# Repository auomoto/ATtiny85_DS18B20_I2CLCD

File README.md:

ATtiny85_TWI_MCP23008_DS18B20_LCD
=================================

This reads a DS18B20 1-Wire temperature sensor and prints the temperature on an LCD screen controlled by an I2C MCP23008 port expander.

Work in progress; this might not work. (see the TWI_SCAN project for later versions?)

ATtiny85 details:

FUSES:	Low:0x62, High:0xDF, Extended:0xFF
	Low=0x62 is 8MHz clock with /8 divider (1MHz CPU clock)
	High=0xDF enables programming, not much else
	Extended=0xFF (no self programming)

To read fuses (lfuse, hfuse, or efuse):
	avrdude -c usbtiny -p attiny85 -U lfuse:r:-:h
	To write fuses (example):
	avrdude -c usbtiny -p attiny85 -U lfuse:w:0x62:m

=========================================================
	
STEP 1: Set up timer interrupts and light the LED.
	The init_ATtiny85() routine sets up the LED on pin 2,
	sets the timer0 clock to run at 1/1024 of the CPU clock
	(so it's 1KHz), and sets up timer interrupts using
	clear-timer-on-compare (CTC) using timer0. The value
	to compare is loaded into the output compare register
	OCR0A (8-bits).

	TTCR0A = Timer/Counter Control Register A for timer0 (set clear timer on compare, CTC, mode)
	TTCR0B = Timer/Counter Control Register B for timer0 (set prescaler by setting CS02, CS01, CS00)
		----------------------
		| CS02 | CS01 | CS00 |
		----------------------
		|   1  |   0  |   1  | is /1024
		----------------------

=========================================================

STEP 2: Set up I2C communications. For I2C, there is one #define
	(__ATtiny85__) and one #include file (usi_twi_master.c). Initialize
	the I2C interface with a call to usi_twi_master_initialize().

	The MCP23008 base address is 0x20. Insert the device address (3 bits),
	shift this left one bit and insert the r/w bit to form the address.
	The base address is handled within MCP23008Write(addr, REGISTER, data)
	so you only put in the 3-bit address as addr.
		Testing the I2C communications is done with the test lights board, an
	LED light bar with eight (out of ten) LEDs connected to the MCP23008.

STEP 2: Rev C.

=========================================================

STEP 3: Connect the LCD display. The LCD is driven off an MCP23008 at
	address 0x01.

=========================================================

STEP 4: Set up the OneWire communications.

=========================================================

STEP 5: Set up the DS18B20 routines.

=========================================================

Note: The usi_twi_master routines are old. Newer versions are in the ATtiny4313 PCA9543 project directory and should replace these. Also change the MCP23008 LCD routines to match the Adafruit backpack pinning since we'll probably buy more of those instead of making our own.

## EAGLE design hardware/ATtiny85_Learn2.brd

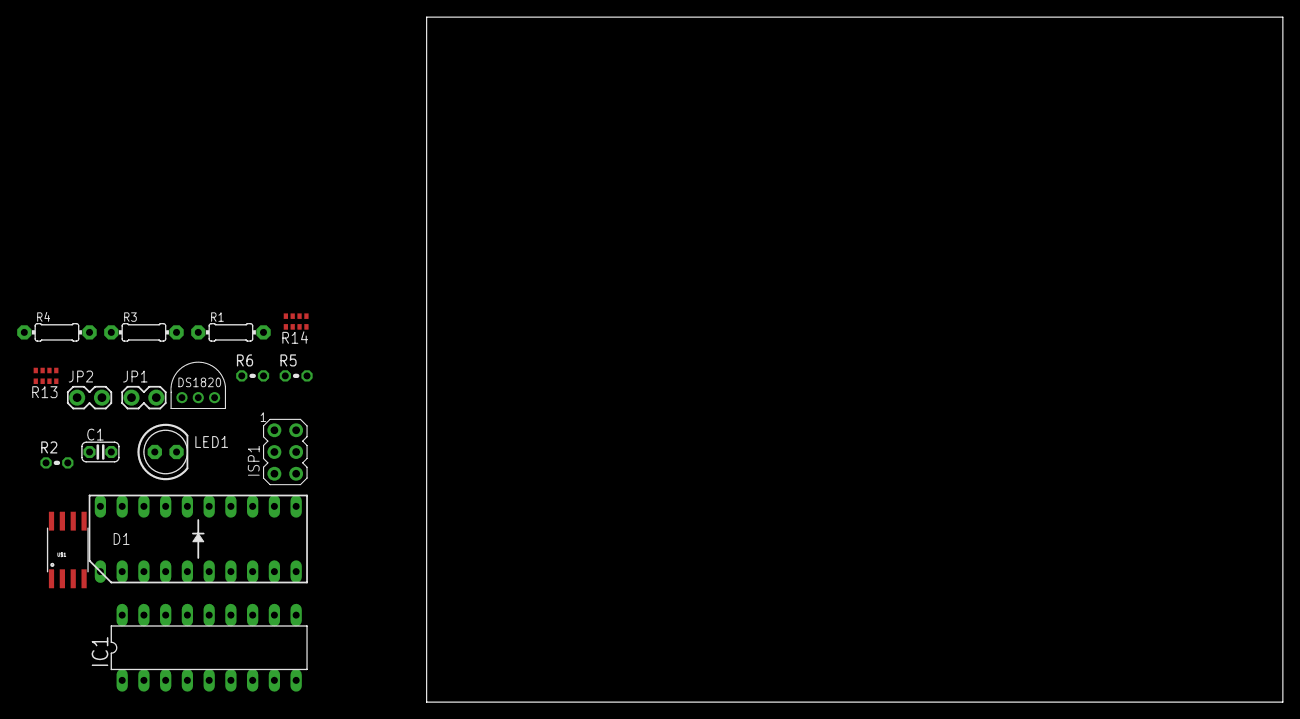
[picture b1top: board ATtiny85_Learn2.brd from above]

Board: 2 copper layers, 100.0 x 80.0 mm, 17 parts (0 on the bottom side), 28 nets, no tracks yet.

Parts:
C1: 0.1uF; C025-024X044
D1: LED_BARGAPH_10
IC1: MCP2300X/P; DIL18
ISP1: AVRISP-6; AVRISP
JP1, JP2: 1X02_LOCK
LED1: LED5MM
R1: 10K; 0204/7
R2, R5: 4K7; 0204V
R3: 220; 0204/7
R4: 4K7; 0204/7
R6: 1K; 0204V
R13, R14: 0603-ARV
U$1: ATtiny85; SO08-EIAJ
U$2: DS1820TO92; DS1820

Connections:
GND: C1.2, D1.13, D1.14, D1.15, D1.16, D1.17, D1.18, D1.19, D1.20, IC1.3, IC1.4, IC1.5, IC1.9, ISP1.6, R3.1, U$1.4, U$2.GND
unnamed: ISP1.5, R1.2, U$1.1
unnamed: ISP1.4, JP2.1, U$1.5
unnamed: ISP1.1, U$1.6
unnamed: LED1.A, U$1.2
unnamed: R4.1, U$1.3, U$2.DQ
unnamed: LED1.K, R3.2
unnamed: IC1.18, R2.2, R5.2, R6.2
unnamed: IC1.2, JP1.2, R5.1
unnamed: IC1.10, R13.1
unnamed: IC1.11, R13.2
unnamed: IC1.12, R13.3
unnamed: IC1.13, R13.4
unnamed: IC1.14, R14.1
unnamed: IC1.15, R14.2
unnamed: IC1.16, R14.3
unnamed: IC1.17, R14.4
unnamed: D1.1, R13.8
unnamed: D1.2, R13.7
unnamed: D1.3, R13.6
unnamed: D1.4, R13.5
unnamed: D1.5, R14.8
unnamed: D1.6, R14.7
unnamed: D1.7, R14.6
unnamed: D1.8, R14.5
unnamed: IC1.6, R6.1
SCL: IC1.1, ISP1.3, JP1.1, JP2.2, R2.1, U$1.7
VCC: C1.1, ISP1.2, R1.1, R4.2, U$1.8, U$2.VDD

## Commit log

2014-01-12 Initial commit.
2014-01-12 The TWI_SCAN project might have a later version.

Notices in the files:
parts and their libraries:
SparkFun-DigitalIC: Licensing: CC v3.0 Share-Alike You are welcome to use this library for commercial purposes.
